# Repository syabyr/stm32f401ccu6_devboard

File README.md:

# stm32f401ccu6_devboard
stm32f401

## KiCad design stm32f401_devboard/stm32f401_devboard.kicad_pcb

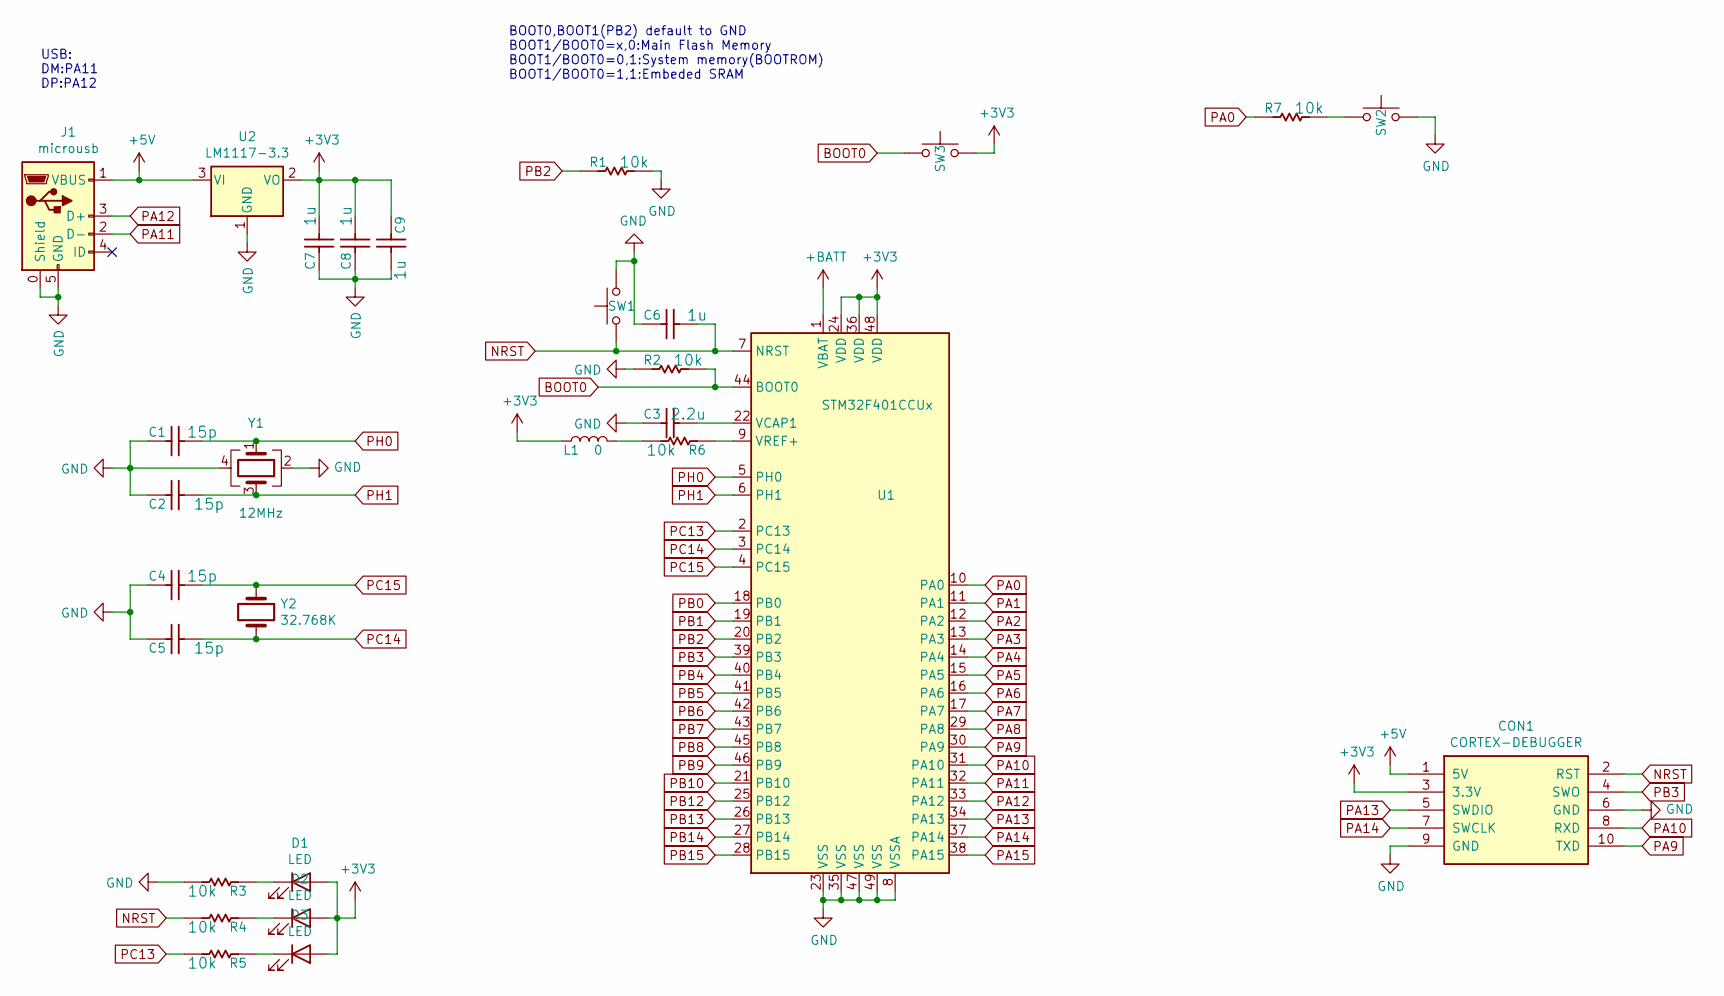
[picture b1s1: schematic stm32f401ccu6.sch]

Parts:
C1, C2, C4, C5: 15p; C_0402_1005Metric
C3: 2.2u; C_0805_2012Metric_Pad1.15x1.40mm_HandSolder
C6, C7, C8: 1u; C_0603_1608Metric_Pad1.05x0.95mm_HandSolder
C9: 1u; C_1206_3216Metric_Pad1.33x1.80mm_HandSolder
CON1: CORTEX-DEBUGGER; debugger_2x05_P1.27mm_Vertical
D1, D2, D3: LED; LED_0805_2012Metric
J1: microusb; MICRO-USB_MICRO-USB-17
L1: 0; L_0603_1608Metric_Pad1.05x0.95mm_HandSolder
R1, R2, R3, R4, R5, R6, R7: 10k; R_0402_1005Metric
SW1, SW2, SW3: SW_Push; turtlekey
U1: STM32F401CCUx; QFN-48-1EP_7x7mm_P0.5mm_EP5.6x5.6mm
U2: LM1117-3.3; SOT-223-3_TabPin2
Y1: 12MHz; Crystal_SMD_3225-4Pin_3.2x2.5mm_HandSoldering
Y2: 32.768K; Crystal_SMD_3215-2Pin_3.2x1.5mm

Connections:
+3V3: C7.2, C8.2, C9.1, CON1.3 (3.3V), D1.2 (A), D2.2 (A), D3.2 (A), L1.1, SW3.2, U1.24 (VDD), U1.36 (VDD), U1.48 (VDD), U2.2 (VO); also elsewhere on the board
+5V: CON1.1 (5V), J1.1 (VBUS), U2.3 (VI); also elsewhere on the board
+BATT: U1.1 (VBAT); also elsewhere on the board
BOOT0: R2.2, SW3.1, U1.44 (BOOT0)
GND: C1.1, C2.1, C3.1, C4.1, C5.1, C6.1, C7.1, C8.1, C9.2, CON1.6 (GND), CON1.9 (GND), J1.0 (Shield), J1.5 (GND), R1.2, R2.1, R3.2, SW1.2, SW2.2, U1.8 (VSSA), U1.23 (VSS), U1.35 (VSS), U1.47 (VSS), U1.49 (VSS), U2.1 (GND), Y1.2, Y1.4; also elsewhere on the board
NRST: C6.2, CON1.2 (RST), R4.2, SW1.1, U1.7 (NRST); also elsewhere on the board
unnamed: C3.2, U1.22 (VCAP1)
unnamed: D1.1 (K), R3.1
unnamed: D2.1 (K), R4.1
unnamed: D3.1 (K), R5.1
unnamed: L1.2, R6.2
unnamed: R6.1, U1.9 (VREF+)
unnamed: R7.2, SW2.1
PA0: R7.1, U1.10 (PA0); also elsewhere on the board
PA1: U1.11 (PA1); also elsewhere on the board
PA2: U1.12 (PA2); also elsewhere on the board
PA3: U1.13 (PA3); also elsewhere on the board
PA4: U1.14 (PA4); also elsewhere on the board
PA5: U1.15 (PA5); also elsewhere on the board
PA6: U1.16 (PA6); also elsewhere on the board
PA7: U1.17 (PA7); also elsewhere on the board
PA8: U1.29 (PA8); also elsewhere on the board
PA9: CON1.10 (TXD), U1.30 (PA9); also elsewhere on the board
PA10: CON1.8 (RXD), U1.31 (PA10); also elsewhere on the board
PA11: J1.2 (D-), U1.32 (PA11); also elsewhere on the board
PA12: J1.3 (D+), U1.33 (PA12); also elsewhere on the board
PA13: CON1.5 (SWDIO), U1.34 (PA13)
PA14: CON1.7 (SWCLK), U1.37 (PA14)
PA15: U1.38 (PA15); also elsewhere on the board
PB0: U1.18 (PB0); also elsewhere on the board
PB1: U1.19 (PB1); also elsewhere on the board
PB2: R1.1, U1.20 (PB2); also elsewhere on the board
PB3: CON1.4 (SWO), U1.39 (PB3); also elsewhere on the board
PB4: U1.40 (PB4); also elsewhere on the board
PB5: U1.41 (PB5); also elsewhere on the board
PB6: U1.42 (PB6); also elsewhere on the board
PB7: U1.43 (PB7); also elsewhere on the board
PB8: U1.45 (PB8); also elsewhere on the board
PB9: U1.46 (PB9); also elsewhere on the board
PB10: U1.21 (PB10); also elsewhere on the board
PB12: U1.25 (PB12); also elsewhere on the board
PB13: U1.26 (PB13); also elsewhere on the board
PB14: U1.27 (PB14); also elsewhere on the board
PB15: U1.28 (PB15); also elsewhere on the board
PC13: R5.2, U1.2 (PC13); also elsewhere on the board
PC14: C5.2, U1.3 (PC14), Y2.2; also elsewhere on the board
PC15: C4.2, U1.4 (PC15), Y2.1; also elsewhere on the board
PH0: C1.2, U1.5 (PH0), Y1.1
PH1: C2.2, U1.6 (PH1), Y1.3

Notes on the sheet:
BOOT0,BOOT1(PB2) default to GND BOOT1/BOOT0=x,0:Main Flash Memory BOOT1/BOOT0=0,1:System memory(BOOTROM) BOOT1/BOOT0=1,1:Embeded SRAM
USB: DM:PA11 DP:PA12

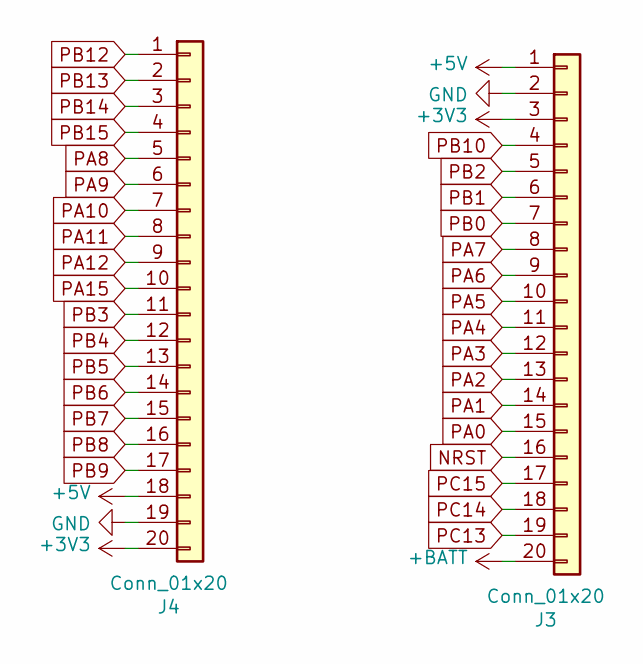
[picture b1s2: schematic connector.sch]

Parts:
J3, J4: Conn_01x20; PinHeader_1x20_P2.54mm_Vertical

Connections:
+3V3: J3.3, J4.20; also elsewhere on the board
+5V: J3.1, J4.18; also elsewhere on the board
+BATT: J3.20; also elsewhere on the board
GND: J3.2, J4.19; also elsewhere on the board
NRST: J3.16; also elsewhere on the board
PA0: J3.15; also elsewhere on the board
PA1: J3.14; also elsewhere on the board
PA2: J3.13; also elsewhere on the board
PA3: J3.12; also elsewhere on the board
PA4: J3.11; also elsewhere on the board
PA5: J3.10; also elsewhere on the board
PA6: J3.9; also elsewhere on the board
PA7: J3.8; also elsewhere on the board
PA8: J4.5; also elsewhere on the board
PA9: J4.6; also elsewhere on the board
PA10: J4.7; also elsewhere on the board
PA11: J4.8; also elsewhere on the board
PA12: J4.9; also elsewhere on the board
PA15: J4.10; also elsewhere on the board
PB0: J3.7; also elsewhere on the board
PB1: J3.6; also elsewhere on the board
PB2: J3.5; also elsewhere on the board
PB3: J4.11; also elsewhere on the board
PB4: J4.12; also elsewhere on the board
PB5: J4.13; also elsewhere on the board
PB6: J4.14; also elsewhere on the board
PB7: J4.15; also elsewhere on the board
PB8: J4.16; also elsewhere on the board
PB9: J4.17; also elsewhere on the board
PB10: J3.4; also elsewhere on the board
PB12: J4.1; also elsewhere on the board
PB13: J4.2; also elsewhere on the board
PB14: J4.3; also elsewhere on the board
PB15: J4.4; also elsewhere on the board
PC13: J3.19; also elsewhere on the board
PC14: J3.18; also elsewhere on the board
PC15: J3.17; also elsewhere on the board

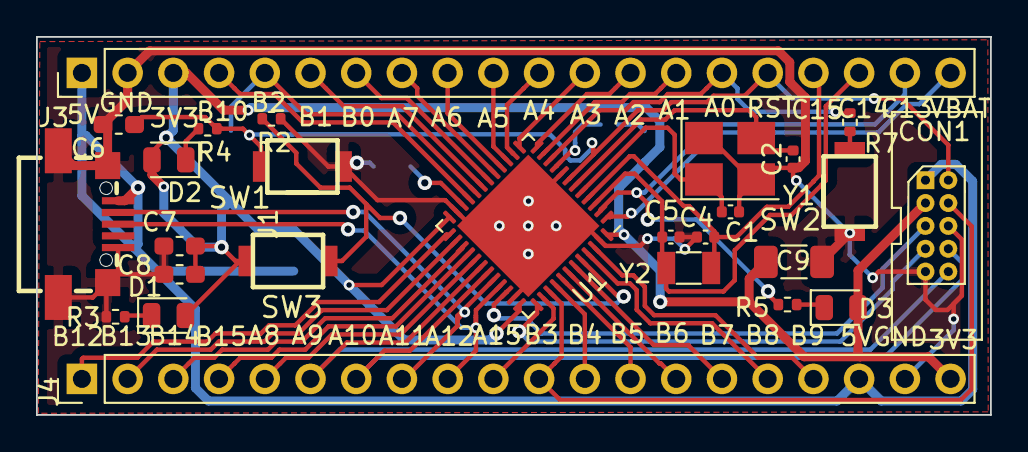
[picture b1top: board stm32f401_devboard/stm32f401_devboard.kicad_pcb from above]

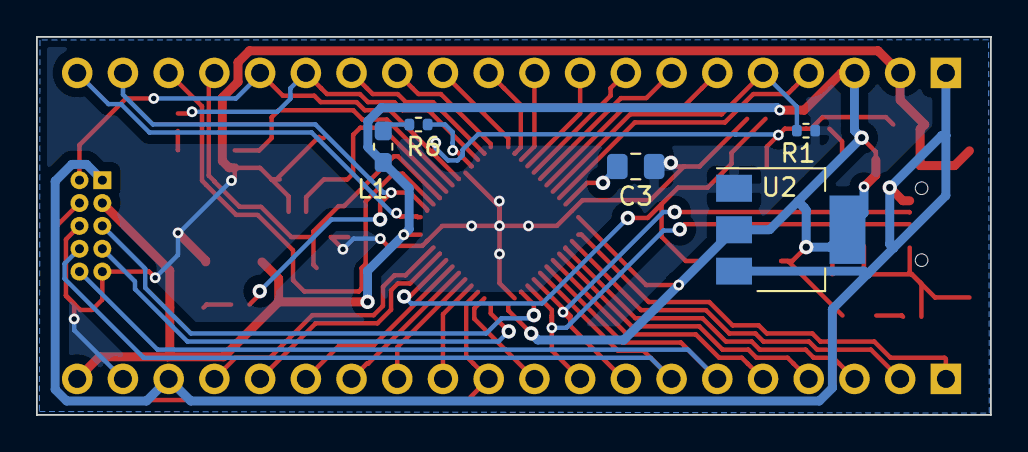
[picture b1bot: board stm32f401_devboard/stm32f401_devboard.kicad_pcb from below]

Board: 2 copper layers, 53.0 x 21.0 mm, 31 parts (5 on the bottom side), 49 nets.

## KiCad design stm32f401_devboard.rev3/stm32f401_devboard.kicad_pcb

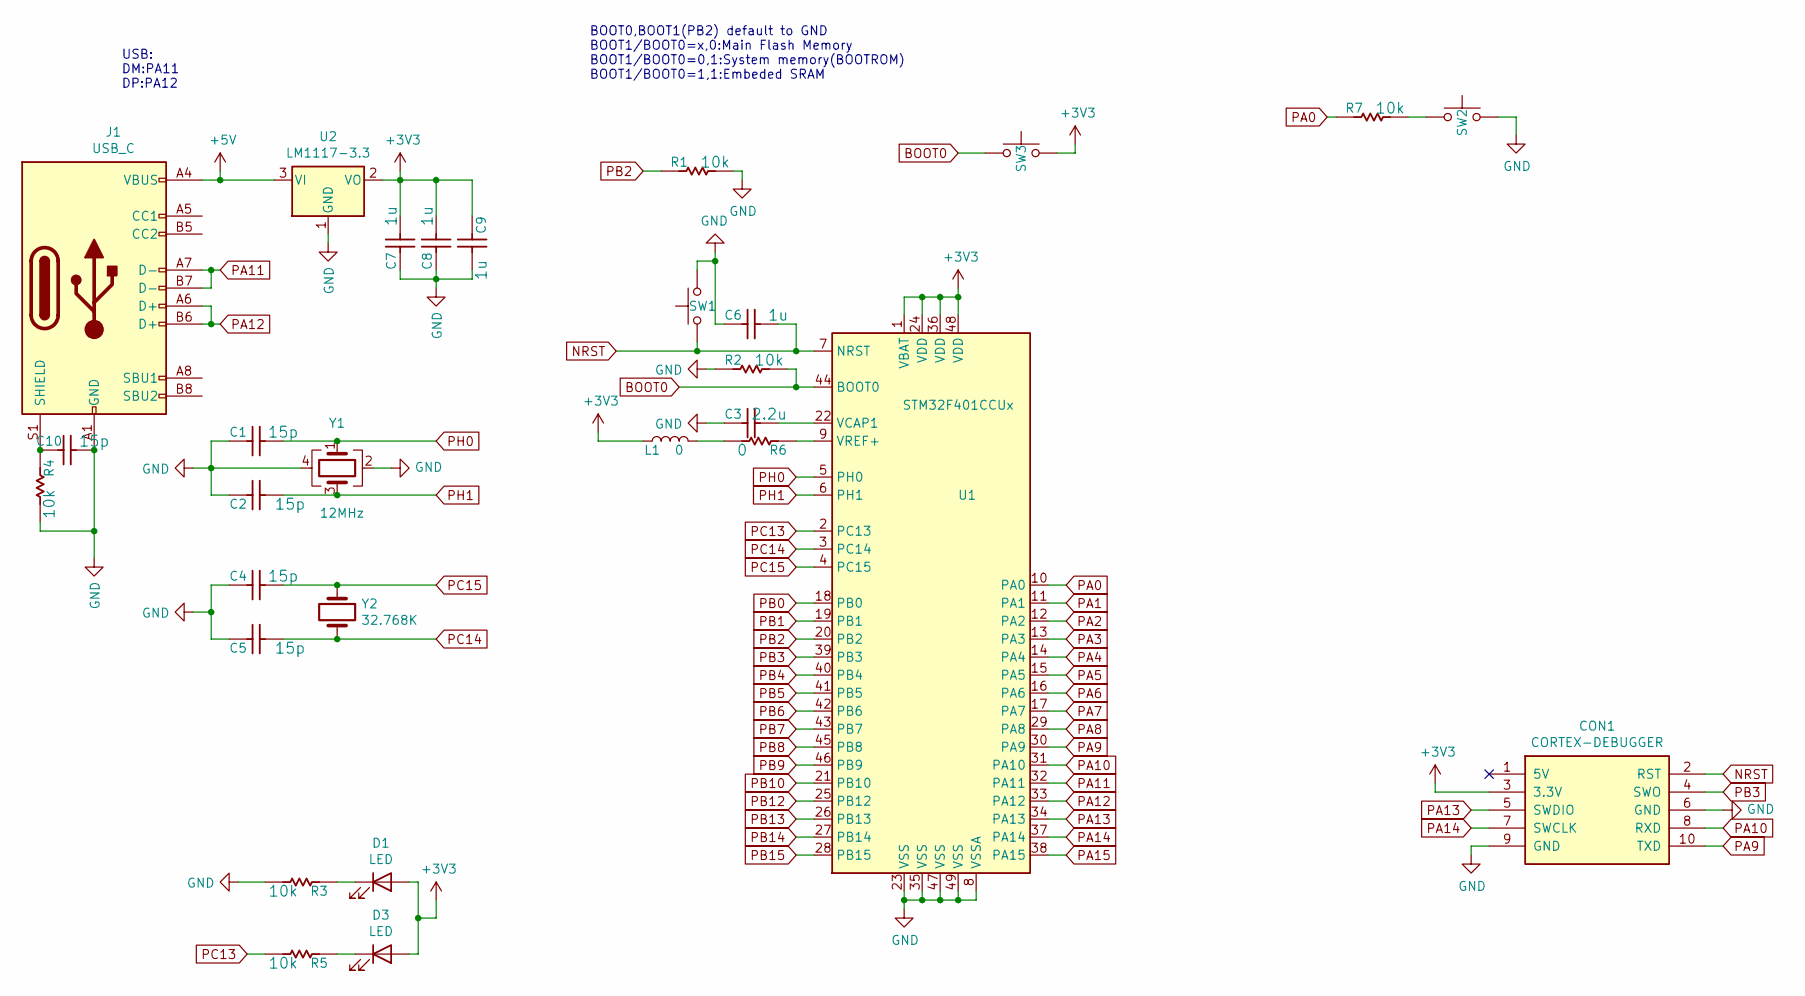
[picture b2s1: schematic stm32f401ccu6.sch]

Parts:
C1, C2, C4, C5, C10: 15p; C_0402_1005Metric
C3: 2.2u; C_0805_2012Metric_Pad1.15x1.40mm_HandSolder
C6, C7, C8, C9: 1u; C_0402_1005Metric_Pad0.74x0.62mm_HandSolder
CON1: CORTEX-DEBUGGER; debugger_2x05_P1.27mm_Vertical
D1, D3: LED; LED_0603_1608Metric_Pad1.05x0.95mm_HandSolder
J1: USB_C
L1: 0; L_0603_1608Metric_Pad1.05x0.95mm_HandSolder
R1, R2, R3, R4, R5, R7: 10k; R_0402_1005Metric
R6: 0; R_0402_1005Metric
SW1, SW2, SW3: SW_Push; turtlekey
U1: STM32F401CCUx; QFN-48-1EP_7x7mm_P0.5mm_EP5.6x5.6mm
U2: LM1117-3.3; SOT-223-3_TabPin2
Y1: 12MHz; Crystal_SMD_3225-4Pin_3.2x2.5mm
Y2: 32.768K; Crystal_SMD_3215-2Pin_3.2x1.5mm

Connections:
+3V3: C7.2, C8.2, C9.1, CON1.3 (3.3V), D1.2 (A), D3.2 (A), L1.1, SW3.2, U1.1 (VBAT), U1.24 (VDD), U1.36 (VDD), U1.48 (VDD), U2.2 (VO); also elsewhere on the board
+5V: J1.A4 (VBUS), J1.A9 (VBUS), J1.B4 (VBUS), J1.B9 (VBUS), U2.3 (VI); also elsewhere on the board
BOOT0: R2.2, SW3.1, U1.44 (BOOT0)
GND: C1.1, C2.1, C3.1, C4.1, C5.1, C6.1, C7.1, C8.1, C9.2, C10.2, CON1.6 (GND), CON1.9 (GND), J1.A1 (GND), J1.A12 (GND), J1.B1 (GND), J1.B12 (GND), R1.2, R2.1, R3.2, R4.2, SW1.2, SW2.2, U1.8 (VSSA), U1.23 (VSS), U1.35 (VSS), U1.47 (VSS), U1.49 (VSS), U2.1 (GND), Y1.2, Y1.4; also elsewhere on the board
NRST: C6.2, CON1.2 (RST), SW1.1, U1.7 (NRST); also elsewhere on the board
unnamed: C3.2, U1.22 (VCAP1)
unnamed: C10.1, J1.S1 (SHIELD), R4.1
unnamed: D1.1 (K), R3.1
unnamed: D3.1 (K), R5.1
unnamed: L1.2, R6.2
unnamed: R6.1, U1.9 (VREF+)
unnamed: R7.2, SW2.1
PA0: R7.1, U1.10 (PA0); also elsewhere on the board
PA1: U1.11 (PA1); also elsewhere on the board
PA2: U1.12 (PA2); also elsewhere on the board
PA3: U1.13 (PA3); also elsewhere on the board
PA4: U1.14 (PA4); also elsewhere on the board
PA5: U1.15 (PA5); also elsewhere on the board
PA6: U1.16 (PA6); also elsewhere on the board
PA7: U1.17 (PA7); also elsewhere on the board
PA8: U1.29 (PA8); also elsewhere on the board
PA9: CON1.10 (TXD), U1.30 (PA9); also elsewhere on the board
PA10: CON1.8 (RXD), U1.31 (PA10); also elsewhere on the board
PA11: J1.A7 (D-), J1.B7 (D-), U1.32 (PA11); also elsewhere on the board
PA12: J1.A6 (D+), J1.B6 (D+), U1.33 (PA12); also elsewhere on the board
PA13: CON1.5 (SWDIO), U1.34 (PA13); also elsewhere on the board
PA14: CON1.7 (SWCLK), U1.37 (PA14); also elsewhere on the board
PA15: U1.38 (PA15); also elsewhere on the board
PB0: U1.18 (PB0); also elsewhere on the board
PB1: U1.19 (PB1); also elsewhere on the board
PB2: R1.1, U1.20 (PB2); also elsewhere on the board
PB3: CON1.4 (SWO), U1.39 (PB3); also elsewhere on the board
PB4: U1.40 (PB4); also elsewhere on the board
PB5: U1.41 (PB5); also elsewhere on the board
PB6: U1.42 (PB6); also elsewhere on the board
PB7: U1.43 (PB7); also elsewhere on the board
PB8: U1.45 (PB8); also elsewhere on the board
PB9: U1.46 (PB9); also elsewhere on the board
PB10: U1.21 (PB10); also elsewhere on the board
PB12: U1.25 (PB12); also elsewhere on the board
PB13: U1.26 (PB13); also elsewhere on the board
PB14: U1.27 (PB14); also elsewhere on the board
PB15: U1.28 (PB15); also elsewhere on the board
PC13: R5.2, U1.2 (PC13)
PC14: C5.2, U1.3 (PC14), Y2.2
PC15: C4.2, U1.4 (PC15), Y2.1
PH0: C1.2, U1.5 (PH0), Y1.1
PH1: C2.2, U1.6 (PH1), Y1.3

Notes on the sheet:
BOOT0,BOOT1(PB2) default to GND BOOT1/BOOT0=x,0:Main Flash Memory BOOT1/BOOT0=0,1:System memory(BOOTROM) BOOT1/BOOT0=1,1:Embeded SRAM
USB: DM:PA11 DP:PA12

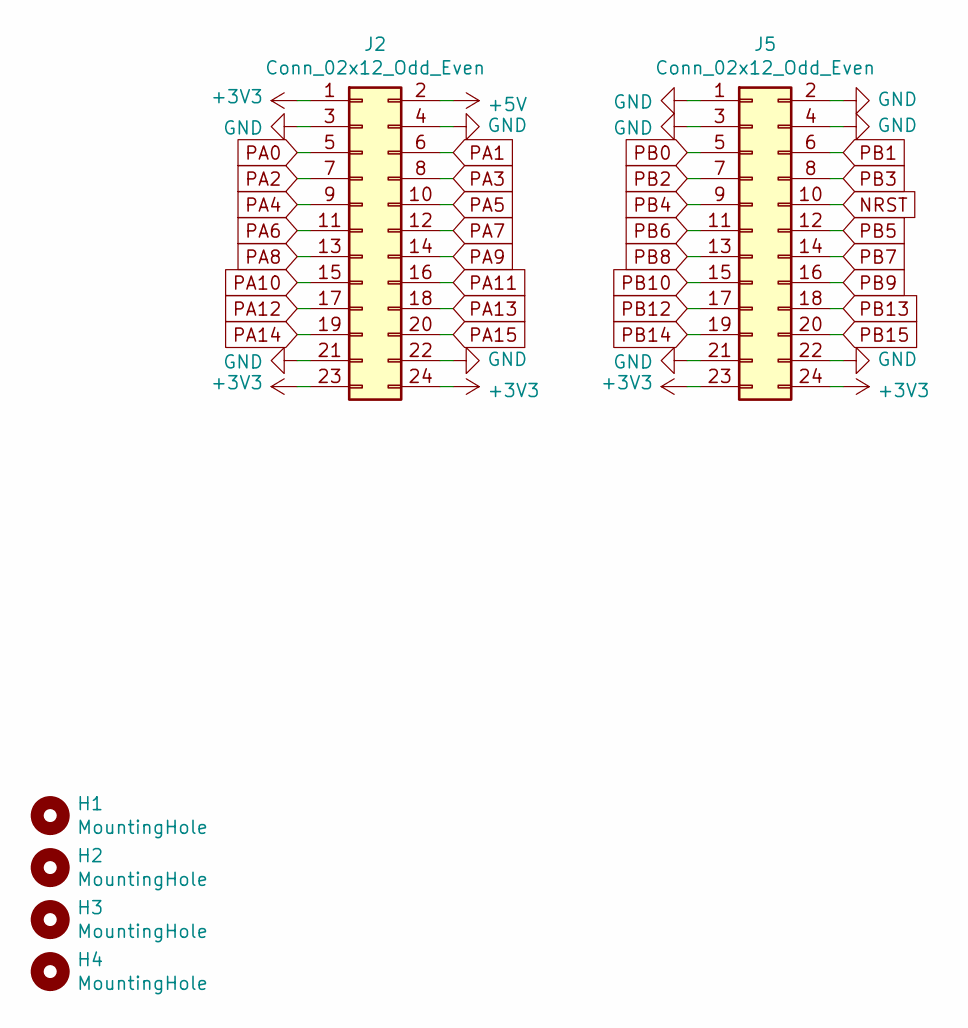
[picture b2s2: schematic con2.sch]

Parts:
H1, H2, H3, H4: MountingHole; MountingHole_3.2mm_M3_ISO7380
J2, J5: Conn_02x12_Odd_Even; PinHeader_2x12_P2.54mm_Vertical

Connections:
+3V3: J2.1, J2.23, J2.24, J5.23, J5.24; also elsewhere on the board
+5V: J2.2; also elsewhere on the board
GND: J2.3, J2.4, J2.21, J2.22, J5.1, J5.2, J5.3, J5.4, J5.21, J5.22; also elsewhere on the board
NRST: J5.10; also elsewhere on the board
PA0: J2.5; also elsewhere on the board
PA1: J2.6; also elsewhere on the board
PA2: J2.7; also elsewhere on the board
PA3: J2.8; also elsewhere on the board
PA4: J2.9; also elsewhere on the board
PA5: J2.10; also elsewhere on the board
PA6: J2.11; also elsewhere on the board
PA7: J2.12; also elsewhere on the board
PA8: J2.13; also elsewhere on the board
PA9: J2.14; also elsewhere on the board
PA10: J2.15; also elsewhere on the board
PA11: J2.16; also elsewhere on the board
PA12: J2.17; also elsewhere on the board
PA13: J2.18; also elsewhere on the board
PA14: J2.19; also elsewhere on the board
PA15: J2.20; also elsewhere on the board
PB0: J5.5; also elsewhere on the board
PB1: J5.6; also elsewhere on the board
PB2: J5.7; also elsewhere on the board
PB3: J5.8; also elsewhere on the board
PB4: J5.9; also elsewhere on the board
PB5: J5.12; also elsewhere on the board
PB6: J5.11; also elsewhere on the board
PB7: J5.14; also elsewhere on the board
PB8: J5.13; also elsewhere on the board
PB9: J5.16; also elsewhere on the board
PB10: J5.15; also elsewhere on the board
PB12: J5.17; also elsewhere on the board
PB13: J5.18; also elsewhere on the board
PB14: J5.19; also elsewhere on the board
PB15: J5.20; also elsewhere on the board

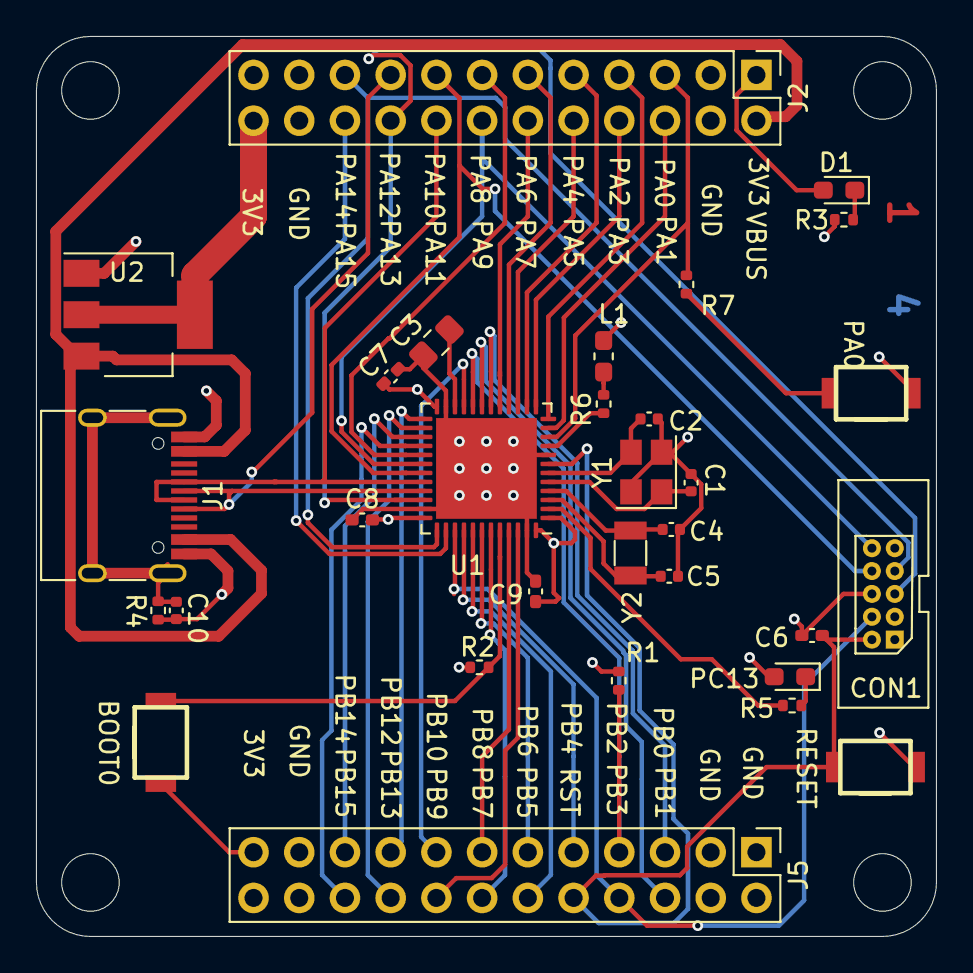
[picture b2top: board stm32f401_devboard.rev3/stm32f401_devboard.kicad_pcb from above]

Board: 4 copper layers, 50.0 x 50.0 mm, 35 parts (0 on the bottom side), 48 nets.

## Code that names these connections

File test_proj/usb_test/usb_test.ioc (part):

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Mcu.Name=STM32F401C(B-C)Ux
Mcu.Package=UFQFPN48
Mcu.UserName=STM32F401CCUx
PA10.Mode=Asynchronous
PA10.Signal=USART1_RX
PA11.Mode=Device_Only
PA11.Signal=USB_OTG_FS_DM
PA12.Mode=Device_Only
PA12.Signal=USB_OTG_FS_DP
PA9.Mode=Asynchronous
PA9.Signal=USART1_TX
PC13-ANTI_TAMP.GPIOParameters=GPIO_Label
PC13-ANTI_TAMP.GPIO_Label=LED
PC13-ANTI_TAMP.Signal=GPIO_Output
PC14-OSC32_IN.Mode=LSE-External-Oscillator
PC14-OSC32_IN.Signal=RCC_OSC32_IN
PC15-OSC32_OUT.Mode=LSE-External-Oscillator
PC15-OSC32_OUT.Signal=RCC_OSC32_OUT
PH0\ -\ OSC_IN.Mode=HSE-External-Oscillator
PH0\ -\ OSC_IN.Signal=RCC_OSC_IN
PH1\ -\ OSC_OUT.Mode=HSE-External-Oscillator
PH1\ -\ OSC_OUT.Signal=RCC_OSC_OUT
RCC.HSE_VALUE=25000000
RCC.SYSCLKFreq_VALUE=84000000
RCC.SYSCLKSource=RCC_SYSCLKSOURCE_PLLCLK
board=custom

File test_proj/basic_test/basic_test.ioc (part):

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Mcu.Name=STM32F401C(B-C)Ux
Mcu.Package=UFQFPN48
Mcu.UserName=STM32F401CCUx
PA10.Mode=Asynchronous
PA10.Signal=USART1_RX
PA13.Mode=Serial_Wire
PA13.Signal=SYS_JTMS-SWDIO
PA14.Mode=Serial_Wire
PA14.Signal=SYS_JTCK-SWCLK
PA9.Mode=Asynchronous
PA9.Signal=USART1_TX
PC13-ANTI_TAMP.GPIOParameters=PinState,GPIO_Label
PC13-ANTI_TAMP.GPIO_Label=LED
PC13-ANTI_TAMP.PinState=GPIO_PIN_RESET
PC13-ANTI_TAMP.Signal=GPIO_Output
PH0\ -\ OSC_IN.Mode=HSE-External-Oscillator
PH0\ -\ OSC_IN.Signal=RCC_OSC_IN
PH1\ -\ OSC_OUT.Mode=HSE-External-Oscillator
PH1\ -\ OSC_OUT.Signal=RCC_OSC_OUT
RCC.HSE_VALUE=25000000
RCC.SYSCLKFreq_VALUE=84000000
RCC.SYSCLKSource=RCC_SYSCLKSOURCE_PLLCLK
board=custom

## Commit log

2021-08-14 first
2021-08-16 rev2
2021-09-01 rev3
2021-09-12 test project
2021-09-18 format
2021-09-18 usb fix
2021-09-18 usb_tools
2021-09-18 ep fix
2022-10-08 upgrade
